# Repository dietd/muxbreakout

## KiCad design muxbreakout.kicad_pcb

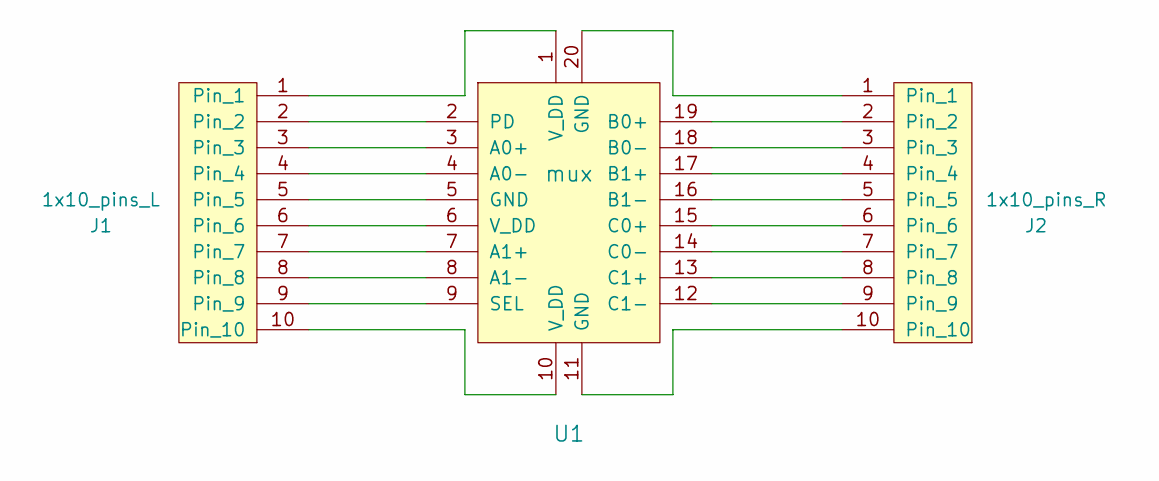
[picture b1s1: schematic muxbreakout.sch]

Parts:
J1: 1x10_pins_L; pins
J2: 1x10_pins_R; pins
U1: mux; muxbreakout

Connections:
unnamed: J1.1, U1.1 (V_DD)
unnamed: J1.2, U1.2 (PD)
unnamed: J1.3, U1.3 (A0+)
unnamed: J1.4, U1.4 (A0-)
unnamed: J1.5, U1.5 (GND)
unnamed: J1.6, U1.6 (V_DD)
unnamed: J1.7, U1.7 (A1+)
unnamed: J1.8, U1.8 (A1-)
unnamed: J1.9, U1.9 (SEL)
unnamed: J1.10, U1.10 (V_DD)
unnamed: J2.1, U1.20 (GND)
unnamed: J2.2, U1.19 (B0+)
unnamed: J2.3, U1.18 (B0-)
unnamed: J2.4, U1.17 (B1+)
unnamed: J2.5, U1.16 (B1-)
unnamed: J2.6, U1.15 (C0+)
unnamed: J2.7, U1.14 (C0-)
unnamed: J2.8, U1.13 (C1+)
unnamed: J2.9, U1.12 (C1-)
unnamed: J2.10, U1.11 (GND)

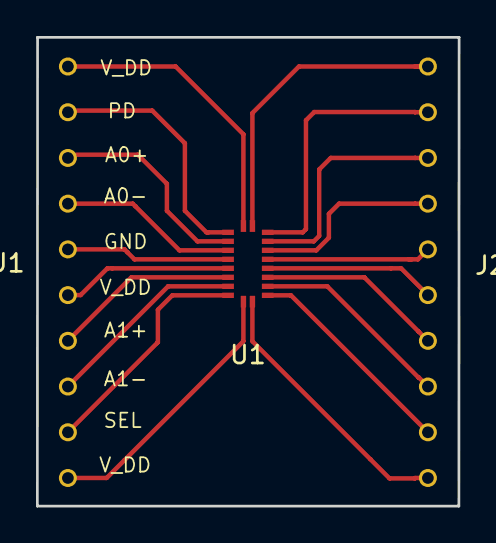
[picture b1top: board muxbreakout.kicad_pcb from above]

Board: 2 copper layers, 23.4 x 26.0 mm, 3 parts (0 on the bottom side), 20 nets.

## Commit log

2019-11-06 added schematics, footprints, and started pcb
2019-11-06 fixed pitch
2019-11-06 pcb edge fixed
